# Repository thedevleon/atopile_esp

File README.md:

# show-and-tell

Giving atopile a try...

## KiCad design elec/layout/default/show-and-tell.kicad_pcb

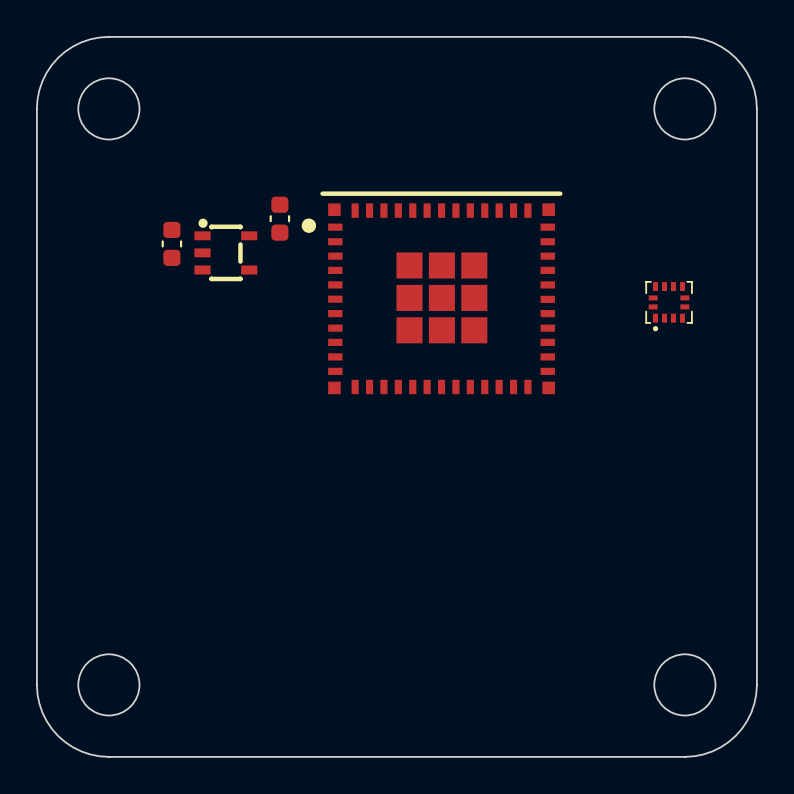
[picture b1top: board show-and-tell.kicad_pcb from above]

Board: 2 copper layers, 40.0 x 40.0 mm, 5 parts (0 on the bottom side), 5 nets, no tracks yet.

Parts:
C1, C2: 10V 10uF X5R ±10% 0603 Multilayer Ceramic Capacit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; C0603
U1: SOT-25_L3.0-W1.6-P0.95-LS2.8-TL
U2: WIFIM-SMD_61P-L16.6-W13.2-P0.80-ESP32-C6-MINI-1-N4
U3: LGA-12_L2.0-W2.0-P0.50-BL

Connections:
accel-gnd: U3.6, U3.7, U3.8
esp.esp-nc: U2.4, U2.7, U2.21, U2.32, U2.33, U2.34, U2.35
power_supply-gnd: C1.2, C2.2, U1.2, U2.1, U2.2, U2.11, U2.14, U2.36, U2.37, U2.38, U2.39, U2.40, U2.41, U2.42, U2.43, U2.44, U2.45, U2.46, U2.47, U2.48, U2.49, U2.50, U2.51, U2.52, U2.53
power_supply-vcc: C2.1, U1.5, U2.3
power_supply.ldo-vcc: C1.1, U1.1, U1.3
